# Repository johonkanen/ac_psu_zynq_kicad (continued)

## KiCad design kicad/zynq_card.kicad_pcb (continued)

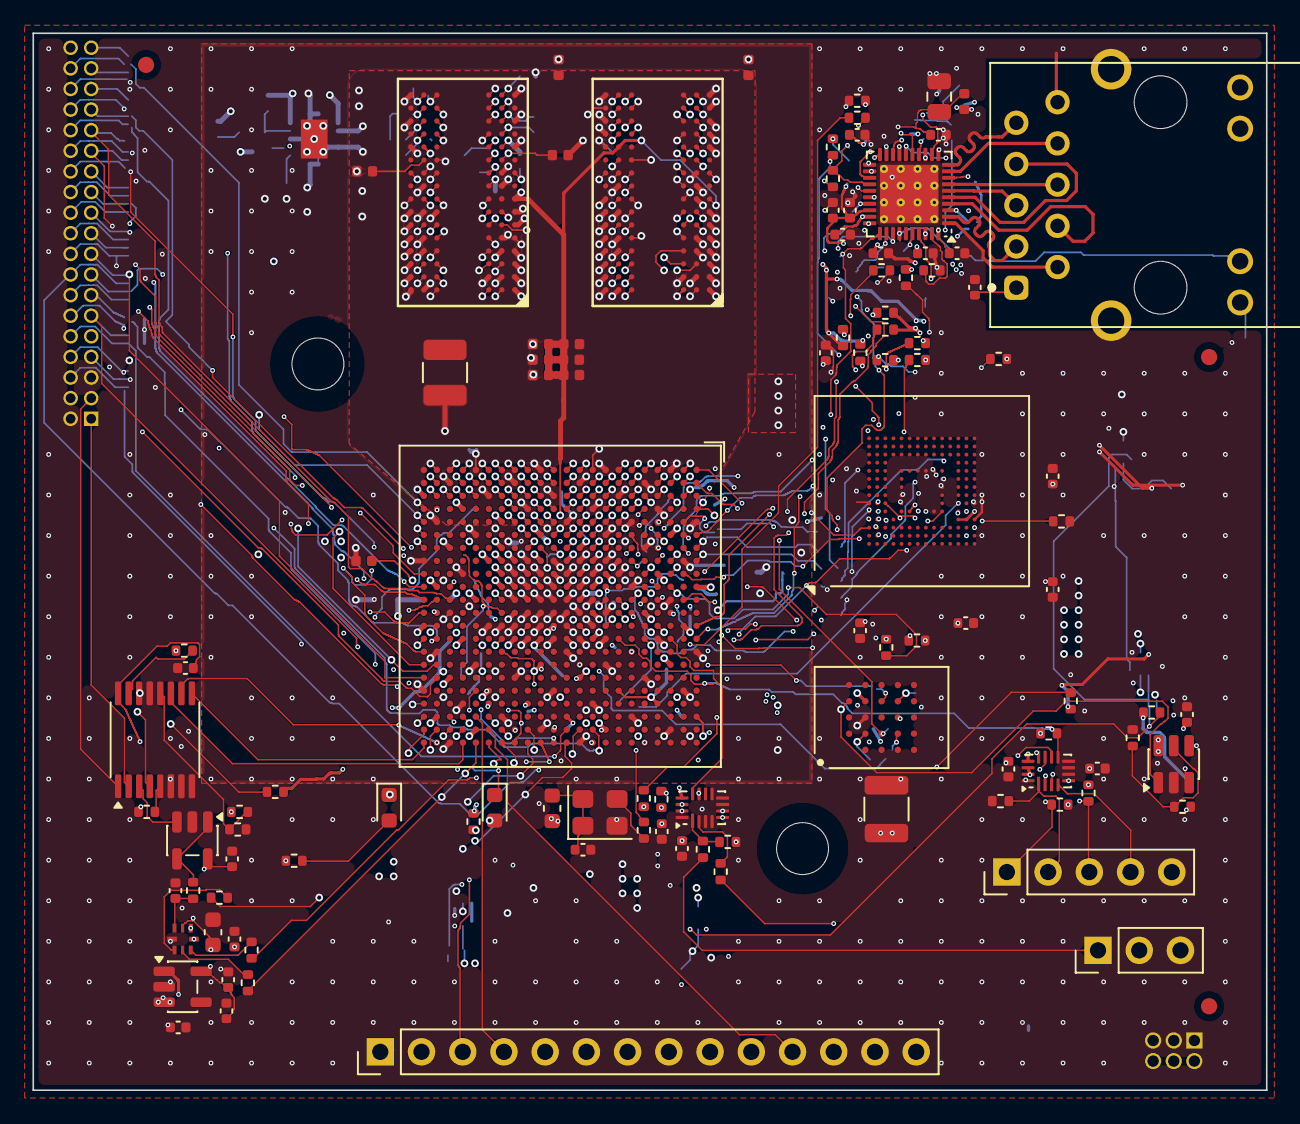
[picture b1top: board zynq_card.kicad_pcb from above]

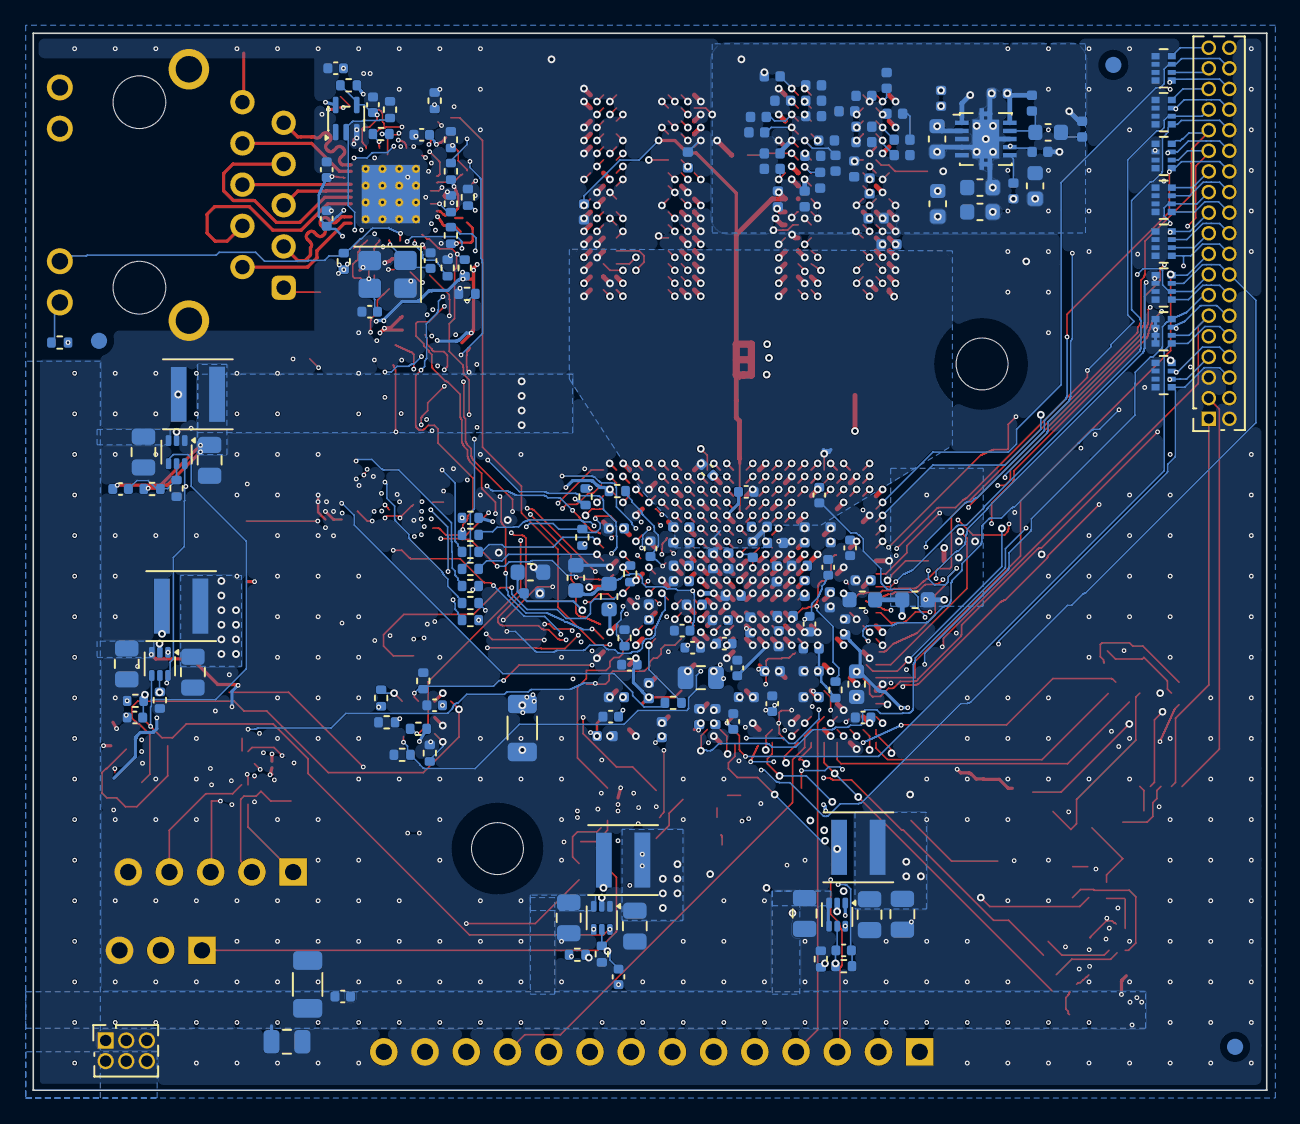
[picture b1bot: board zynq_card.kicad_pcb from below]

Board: 8 copper layers, 76.0 x 65.1 mm, 304 parts (192 on the bottom side), 262 nets.

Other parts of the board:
FID1, FID2, FID3, FID4, FID5, FID6: Fiducial; Fiducial_1mm_Mask2mm
H1, H2: MountingHole_3.2mm_M3

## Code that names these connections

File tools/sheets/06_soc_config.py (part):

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        "their pull-ups sit with the parts on their sheets. JTAG J1 is 3.3 V (FTDI mini-module), shifted by U601.",
        g(10), g(14))  # noqa: F405

# ---------------------------------------------------------------- unit 6: bank 500 (QSPI, straps, GPIO, PS_CLK/POR)
MIO0 = {"A1": ("qspi_cs_n", "output"), "A2": ("qspi_io0", "bidirectional"), "F6": ("qspi_io1", "bidirectional"),
        "E4": ("qspi_io2", "bidirectional"), "A3": ("qspi_io3", "bidirectional"), "A4": ("qspi_sclk", "output"),
        "D5": ("emmc_rst_n", "output"), "A6": ("eth_rst_n", "output"), "B6": ("eth_int_n", "input"),  # MIO13/14
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    if ball in MIO0:
        attach(sh, u6, ball, "hlabel", MIO0[ball][0], n=8, shape=MIO0[ball][1], side="left")  # noqa: F405
    elif ball == "E5":  # MIO8: QSPI feedback clock, only its strap (keep the stub < 10 mm)
        attach(sh, u6, ball, "label", "qspi_fbclk", n=8, side="left")  # noqa: F405
    elif ball in ("B3", "C6"):  # VCCO_MIO0 (stacked)
        if ball == "B3":
            attach(sh, u6, ball, "power", "1V8", n=4, side="left")  # noqa: F405
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        else:  # 28-39 (USB0, unused), 46, 47
            attach(sh, u7, ball, "nc")  # noqa: F405
    elif name == "PS_MIO_VREF_501":
        attach(sh, u7, ball, "label", "ps_mio_vref", n=8, side="left")  # noqa: F405
    elif name == "PS_SRST_B_501":
        attach(sh, u7, ball, "label", "ps_srst_n", n=8, side="left")  # noqa: F405
    elif ball == "A10":  # VCCO_MIO1 (stacked)
        attach(sh, u7, ball, "power", "1V8", n=4, side="left")  # noqa: F405
sh.text("MIO28-39 (USB0), 46, 47: spare", g(148), g(150))  # noqa: F405
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c_vref = ref("C")
_, ct, cb = vert2(sh, "C", c_vref, VX + g(18), VY, "10n", text="right")  # noqa: F405
set_field(sh, c_vref, "Footprint", C0402)  # noqa: F405
sh.wire(ct, up(ct, 2)); sh.label("ps_mio_vref", *up(ct, 2), 90)  # noqa: F405
sh.wire(cb, down(cb, 2)); power_at(sh, "GND", down(cb, 2), "down")  # noqa: F405
fx = VX + g(26)  # noqa: F405
sh.label("ps_mio_vref", fx, VY - g(4), 90); sh.wire((fx, VY - g(4)), (fx, VY)); sh.pwr_flag(fx, VY, 180)  # noqa: F405
pull("ps_srst_n", "1V8", "10k", VX + g(34), VY)  # noqa: F405

# ---------------------------------------------------------------- unit 1: bank 0
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         "G9": ("power", "GND"), "M12": ("power", "GND"), "L11": ("power", "GND"), "L12": ("power", "GND"),
         "M11": ("power", "GND"), "T7": ("power", "1V8"), "T8": ("power", "1V8"), "T10": ("power", "1V8"),
         "K11": ("power", "1V8"), "R12": ("power", "1V8"), "G10": ("nc", None),
         "T12": ("label", "cfg_done"), "T14": ("label", "cfg_init_n"), "T11": ("label", "cfg_program_n"),
         "G11": ("label", "jtag_tck_1v8"), "H13": ("label", "jtag_tdi_1v8"), "G14": ("label", "jtag_tdo_1v8"),
         "G12": ("label", "jtag_tms_1v8")}
u1 = place_unit(sh, "XC7Z020-CLG484", "U20", g(290), g(30), 1)  # noqa: F405
for ball, (kind, net) in UNIT1.items():
    attach(sh, u1, ball, kind, net, n=6, side="left")  # noqa: F405
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set_field(sh, "U601", "Footprint", "Package_DFN_QFN:UQFN-16_1.8x2.6mm_P0.4mm")  # noqa: F405
for pin, kind, net in ((14, "power", "3V3"), (15, "power", "3V3"), (16, "power", "3V3"), (5, "power", "3V3"),
                       (6, "power", "GND"), (7, "power", "GND"), (8, "power", "GND"), (13, "power", "1V8"),
                       (1, "label", "jtag_tck"), (2, "label", "jtag_tdi"), (3, "label", "jtag_tms"),
                       (4, "label", "jtag_tdo"), (12, "label", "jtag_tck_1v8"), (11, "label", "jtag_tdi_1v8"),
                       (10, "label", "jtag_tms_1v8"), (9, "label", "jtag_tdo_1v8")):
    attach(sh, u, pin, kind, net, n=4)  # noqa: F405
decap("3V3", JX - g(14), JY + g(24))  # noqa: F405
decap("1V8", JX + g(20), JY + g(24))  # noqa: F405
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
j1 = sh.place("Conn_01x05", "J1", g(318), g(178), value="JTAG 3V3")  # noqa: F405
set_field(sh, "J1", "Footprint", "Connector_PinHeader_2.54mm:PinHeader_1x05_P2.54mm_Vertical")  # noqa: F405
for pin, net in ((1, "jtag_tdi"), (2, "jtag_tck"), (3, "jtag_tms"), (4, "jtag_tdo")):
    p = j1.pin(pin)
    sh.wire(p, left(p, 6)); sh.label(net, *left(p, 6), 180)  # noqa: F405
p = j1.pin(5)
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
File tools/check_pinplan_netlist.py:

#!/usr/bin/env python3
"""Phase-2 closing check: every PL pin-plan signal and every MIO signal sits on its U20 ball in the netlist, and the
net reaches the part at the far end.

    tools/check_pinplan_netlist.py      (after tools/build_schematic.sh, which exports work/zynq_card_net.xml)

- PL: vivado/pinplan/zynq_pinplan.csv (signal -> ball). The net on that ball must carry the signal's name, and the far
  end is J3.<n> from the note column (j3), J5.<n> (lcd, the sheet-13 order), the ADC parts (adc) or the LED (led).
- MIO: MIO number -> ball from the XC7Z020-CLG484 symbol pin names (PS_MIO<n>_50x), checked against
  vivado/pinplan/ps7_mio.csv (Vivado's PS7 settings); the expected net and far-end pad per MIO are below.
  Every other MIO ball must be unconnected.
"""
import csv
import os
import sys
import xml.etree.ElementTree as ET

TOOLS = os.path.dirname(os.path.abspath(__file__))
ROOT = os.path.dirname(TOOLS)
sys.path.insert(0, os.path.join(TOOLS, "p2k"))
from p2k.sexpr import find, find_all, load  # noqa: E402

NET = os.path.join(ROOT, "work", "zynq_card_net.xml")
LIB = os.path.join(ROOT, "lib", "zynq_card.kicad_sym")
PP = os.path.join(ROOT, "vivado", "pinplan", "zynq_pinplan.csv")
PS7 = os.path.join(ROOT, "vivado", "pinplan", "ps7_mio.csv")

LCD = ["t_irq", "t_do", "t_din", "t_cs_n", "t_clk", "lcd_mosi", "lcd_led", "lcd_sck", "lcd_miso",
       "lcd_dc", "lcd_reset_n", "lcd_cs_n"]  # J5 pins 1-12 (sheet 13)
PL_FAR = {"adc_cs_n": ("R1210", "1"), "adc_sclk": ("R1211", "1"), "adc_sdo": ("R1212", "1"),
          "adbsel0": ("U1201", "11"), "adbsel1": ("U1201", "10"), "adbsel2": ("U1201", "9"),
          "led0_n": ("D1101", None), "led1_n": ("D1102", None),
          **{s: ("J5", str(i)) for i, s in enumerate(LCD, 1)}}
LOCAL = {"led0_n": "/11 soc_pl/led0_n", "led1_n": "/11 soc_pl/led1_n"}

# MIO: (net, far-end ref, pin or None, ps7_mio.csv peripheral)
MIO = {1: ("qspi_cs_n", "U801", "C2", "Quad SPI Flash"), 2: ("qspi_io0", "U801", "D3", "Quad SPI Flash"),
       3: ("qspi_io1", "U801", "D2", "Quad SPI Flash"), 4: ("qspi_io2", "U801", "C4", "Quad SPI Flash"),
       5: ("qspi_io3", "U801", "D4", "Quad SPI Flash"), 6: ("qspi_sclk", "U801", "B2", "Quad SPI Flash"),
       7: ("emmc_rst_n", "U1001", "K5", "GPIO"), 8: ("/06 soc_config/qspi_fbclk", "R607", None, "Quad SPI Flash"),
       13: ("eth_rst_n", "U902", "2", "GPIO"), 14: ("eth_int_n", "U901", "31", "GPIO"),
       16: ("rgmii_txc", "R901", None, "Enet 0"), 17: ("rgmii_txd0", "R903", None, "Enet 0"),
       18: ("rgmii_txd1", "R904", None, "Enet 0"), 19: ("rgmii_txd2", "R905", None, "Enet 0"),
       20: ("rgmii_txd3", "R906", None, "Enet 0"), 21: ("rgmii_tx_ctl", "R902", None, "Enet 0"),
       22: ("rgmii_rxc", "R907", None, "Enet 0"), 23: ("rgmii_rxd0", "R909", None, "Enet 0"),
       24: ("rgmii_rxd1", "R910", None, "Enet 0"), 25: ("rgmii_rxd2", "R911", None, "Enet 0"),
       26: ("rgmii_rxd3", "R912", None, "Enet 0"), 27: ("rgmii_rx_ctl", "R908", None, "Enet 0"),
       40: ("sd_clk", "R1001", None, "SD 0"), 41: ("sd_cmd", "U1001", "M5", "SD 0"),
       42: ("sd_dat0", "U1001", "A3", "SD 0"), 43: ("sd_dat1", "U1001", "A4", "SD 0"),
       44: ("sd_dat2", "U1001", "A5", "SD 0"), 45: ("sd_dat3", "U1001", "B2", "SD 0"),
       48: ("uart_tx", "U1301", "11", "UART 1"), 49: ("uart_rx", "U1301", "12", "UART 1"),
       50: ("i2c_scl", "R1305", None, "I2C 0"), 51: ("i2c_sda", "R1306", None, "I2C 0"),
       52: ("mdc", "U901", "13", "Enet 0"), 53: ("mdio", "U901", "14", "Enet 0")}


def main():
    x = ET.parse(NET).getroot()
    net_of, nodes = {}, {}
    for n in x.iter("net"):
        ns = {(d.get("ref"), d.get("pin")) for d in n.iter("node")}
        nodes[n.get("name")] = ns
        for k in ns:
            net_of[k] = n.get("name")
    fails = []

    def check(what, ball, want, ref, pin):
        got = net_of.get(("U20", ball))
        want = want if want.startswith("/") else "/" + want
        if got != want:
            fails.append(f"{what}: U20.{ball} on {got}, want {want}")
        elif not any(r == ref and (pin is None or p == pin) for r, p in nodes[got]):
            fails.append(f"{what}: {got} does not reach {ref}{'.' + pin if pin else ''}")

    with open(PP) as f:
        pl = list(csv.DictReader(f))
    for r in pl:
        s = r["signal"]
        if r["group"] == "j3":
            far = ("J3", r["note"].split(".")[1])
        else:
            far = PL_FAR[s]
        check(f"PL {s}", r["ball"], LOCAL.get(s, s), *far)

    sym = next(s for s in find_all(load(LIB), "symbol") if s[1] == "XC7Z020-CLG484")
    ball = {}
    for sub in find_all(sym, "symbol"):
        for p in find_all(sub, "pin"):
            name = find(p, "name")[1]
            if name.startswith("PS_MIO") and name[6:].split("_")[0].isdigit():
                ball[int(name[6:].split("_")[0])] = find(p, "number")[1]
    assert len(ball) == 54, len(ball)
    with open(PS7) as f:
        ps7 = {int(r[0]): r[1] for r in csv.reader(f) if r and r[0].isdigit()}
    for mio, b in sorted(ball.items()):
        if mio in MIO:
            net, ref, pin, periph = MIO[mio]
            if ps7.get(mio) != periph:
                fails.append(f"MIO{mio}: ps7_mio.csv has {ps7.get(mio)!r}, want {periph!r}")
            check(f"MIO{mio}", b, net, ref, pin)
        else:
            got = net_of.get(("U20", b))
            if got and not got.startswith("unconnected-"):
                fails.append(f"MIO{mio} (spare): U20.{b} on {got}")
    for f_ in fails:
        print("FAIL", f_)
    print(f"check_pinplan_netlist: {len(pl)} PL signals, {len(MIO)} MIO signals, "
          f"{54 - len(MIO)} spare MIO open; {len(fails)} failures")
    return 1 if fails else 0


if __name__ == "__main__":
    sys.exit(main())

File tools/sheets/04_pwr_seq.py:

#!/usr/bin/env python3
"""Sheet 4 (pwr_seq): the enable chain pull-ups and the PS_POR_B supervisor (ZYNQ_PCB_NOTES.md §3).

The Ti135 card's sheet 4 (power-good chain + TPS3808 into CRESET_N), re-ordered for the Zynq:
- pg_1v0 = PG(1V0), R401 100 k to 5V0 -> EN of 1V8. 1V0 (VCCPINT/VCCINT/VCCBRAM) first.
- pg_1v8 = PG(1V8), R402 100 k to 5V0 -> EN of 3V3 and 1V35. So 1V8 (VCCAUX, VCCPAUX, VCCO_MIO, VCCO_0) is at 95 %
  before 3V3 starts: VCCO - VCCAUX <= 2.625 V holds without using T_VCCO2VCCAUX.
- DDR3_VTT_EN = PG(3V3) & PG(1V35) (wired AND), pulled up by R25 (20 k to 3V3, sheet 1, REUSE_LOG E3): TPS51200 EN
  (VIH 1.7 V, abs max 6.5 V). The same node is U401 ~MR, the last power-good.
  ~MR has a 70-90 k internal pull-up to VDD (1V8): the node settles at about 3.0 V, inside V_MR <= 6.5 V
  (SBVS050 Rec. op.), and the 14 uA it feeds into 1V8 is harmless.
- TLV62585 PG is low while EN is low or in UVLO (SLVSDE5F Table 1), so a rail that drops pulls every later EN low.
U401 TPS3808G01: VDD = 1V8 (the PS_POR_B pull-up rail, R608 on sheet 6), so RESET is valid before PS_POR_B can rise.
- SENSE watches 1V0 (VCCPINT) through R403/R404: 0.405 V x (1 + 121/100) = 0.895 V. Power-off: PS_POR_B asserts
  before VCCPINT falls to 0.80 V and stays low while VDD (1V8, light load, ~400 uF) is up (DS187 eFUSE rule).
- CT = VDD: t_D = 300 ms (180-420 ms) after both ~MR and SENSE are good. DS187 Table 23 (33.33 MHz): PS_POR_B must not
  be released inside T_SLW of the last PL supply (VCCINT/VCCBRAM/VCCAUX/VCCO_0, i.e. 1V8 here) reaching 250 mV.
  Our release is 180-425 ms after it, outside every row (default 12..40, eFUSE CRC -16..12, PLL bypass -27..13,
  eFUSE + bypass -746..-705 ms). CT open (12-28 ms) would fall inside the eFUSE and bypass windows.
- RESET is open drain onto ps_por_n (R608 10 k to 1V8 on sheet 6). T_PSPOR (100 us) is met by far.
"""
from _common import *  # noqa: F401,F403

R0402 = "Resistor_SMD:R_0402_1005Metric"
sh = sheet("04_pwr_seq.kicad_sch")  # noqa: F405
sh.text("Power-up (ZYNQ_PCB_NOTES.md §3): 5V0 -> 1V0 -> pg_1v0 -> 1V8 -> pg_1v8 -> 3V3 + 1V35 -> DDR3_VTT_EN (TPS51200 VTT)\n"
        "-> U401 TPS3808G01 (CT = VDD: 300 ms) -> ps_por_n (PS_POR_B). Each TLV62585 ramps in 0.9 ms (DS187: 0.2-50 ms).\n"
        "300 ms keeps PS_POR_B release outside the DS187 Table 23 secure lockdown window in every boot configuration.",
        g(14), g(14))  # noqa: F405


def pullup(ref, net, x, y, rail, text):
    n = (x, y)
    hlabel_left(sh, net, n, 4)  # noqa: F405
    _, rt, rb = vert2(sh, "R", ref, n[0] + g(4), n[1] - g(5), "100k", text="right")  # noqa: F405
    sh.wire(n, (rb[0], n[1]), rb)
    sh.wire(rt, up(rt, 2)); power_at(sh, rail, up(rt, 2), "up")  # noqa: F405
    set_field(sh, ref, "Footprint", R0402)  # noqa: F405
    sh.text(text, x - g(10), y + g(4))  # noqa: F405


pullup("R401", "pg_1v0", g(40), g(50), "5V0", "pg_1v0 = PG(1V0) -> EN of 1V8")  # noqa: F405
pullup("R402", "pg_1v8", g(40), g(80), "5V0", "pg_1v8 = PG(1V8) -> EN of 3V3 and 1V35")  # noqa: F405

# supervisor
X, Y = g(130), g(66)  # noqa: F405
u = sh.place("TPS3808DBV", "U401", X, Y, value="TPS3808G01DBVR", fields={"MPN": "TPS3808G01DBVR"})
set_field(sh, "U401", "Footprint", "Package_TO_SOT_SMD:SOT-23-6")  # noqa: F405
rst, gnd, mr, ct, sense, vdd = (u.pin(k) for k in (1, 2, 3, 4, 5, 6))
hlabel_left(sh, "DDR3_VTT_EN", mr, 12)  # noqa: F405
sh.text("DDR3_VTT_EN = PG(3V3) & PG(1V35), wired AND,\npull-up R25 20k to 3V3 (sheet 1) = TPS51200 EN",
        mr[0] - g(34), mr[1] + g(9))  # noqa: F405
sh.wire(vdd, up(vdd, 3)); power_at(sh, "1V8", up(vdd, 3), "up")  # noqa: F405
# CT to VDD: 300 ms
sh.wire(ct, left(ct, 3)); power_at(sh, "1V8", left(ct, 3), "left")  # noqa: F405
sh.text("CT = VDD (1V8): t_D = 300 ms", mr[0] - g(34), mr[1] + g(15))  # noqa: F405
# SENSE: 1V0 divider, 0.895 V, on the local label por_sense
q = left(sense, 3)  # noqa: F405
sh.wire(sense, q); sh.wire(q, up(q, 2)); sh.label("por_sense", *up(q, 2), 90)  # noqa: F405
xs, ys = g(84), g(92)  # noqa: F405
_, st, sb = vert2(sh, "R", "R403", xs, ys - g(5), "121k", text="left")  # noqa: F405
sh.wire(st, up(st, 2)); power_at(sh, "1V0", up(st, 2), "up")  # noqa: F405
_, bt, bb = vert2(sh, "R", "R404", xs, ys + g(5), "100k", text="left")  # noqa: F405
sh.wire(sb, (xs, ys), bt); sh.junction(xs, ys)
sh.wire((xs, ys), right((xs, ys), 4)); sh.label("por_sense", *right((xs, ys), 4), 0)  # noqa: F405
sh.wire(bb, down(bb, 2)); power_at(sh, "GND", down(bb, 2), "down")  # noqa: F405
for r in ("R403", "R404"):
    set_field(sh, r, "Footprint", R0402)  # noqa: F405
sh.text("SENSE divider: 1V0 < 0.895 V -> reset\n(asserted before VCCPINT reaches 0.80 V)", xs + g(4), ys + g(7))  # noqa: F405
sh.wire(gnd, down(gnd, 2)); power_at(sh, "GND", down(gnd, 2), "down")  # noqa: F405
hlabel_right(sh, "ps_por_n", rst, 8, "output")  # noqa: F405
sh.text("open drain; 10k pull-up to 1V8\nis R608 on sheet 6", rst[0] + g(2), rst[1] + g(4))  # noqa: F405
_, ct2, cb2 = vert2(sh, "C", "C401", X + g(22), Y - g(14), "100n", text="right")  # noqa: F405
sh.wire(ct2, up(ct2, 2)); power_at(sh, "1V8", up(ct2, 2), "up")  # noqa: F405
sh.wire(cb2, down(cb2, 2)); power_at(sh, "GND", down(cb2, 2), "down")  # noqa: F405
set_field(sh, "C401", "Footprint", "Capacitor_SMD:C_0402_1005Metric")  # noqa: F405
sh.save()
print("04_pwr_seq: R401-R404, U401, C401")
